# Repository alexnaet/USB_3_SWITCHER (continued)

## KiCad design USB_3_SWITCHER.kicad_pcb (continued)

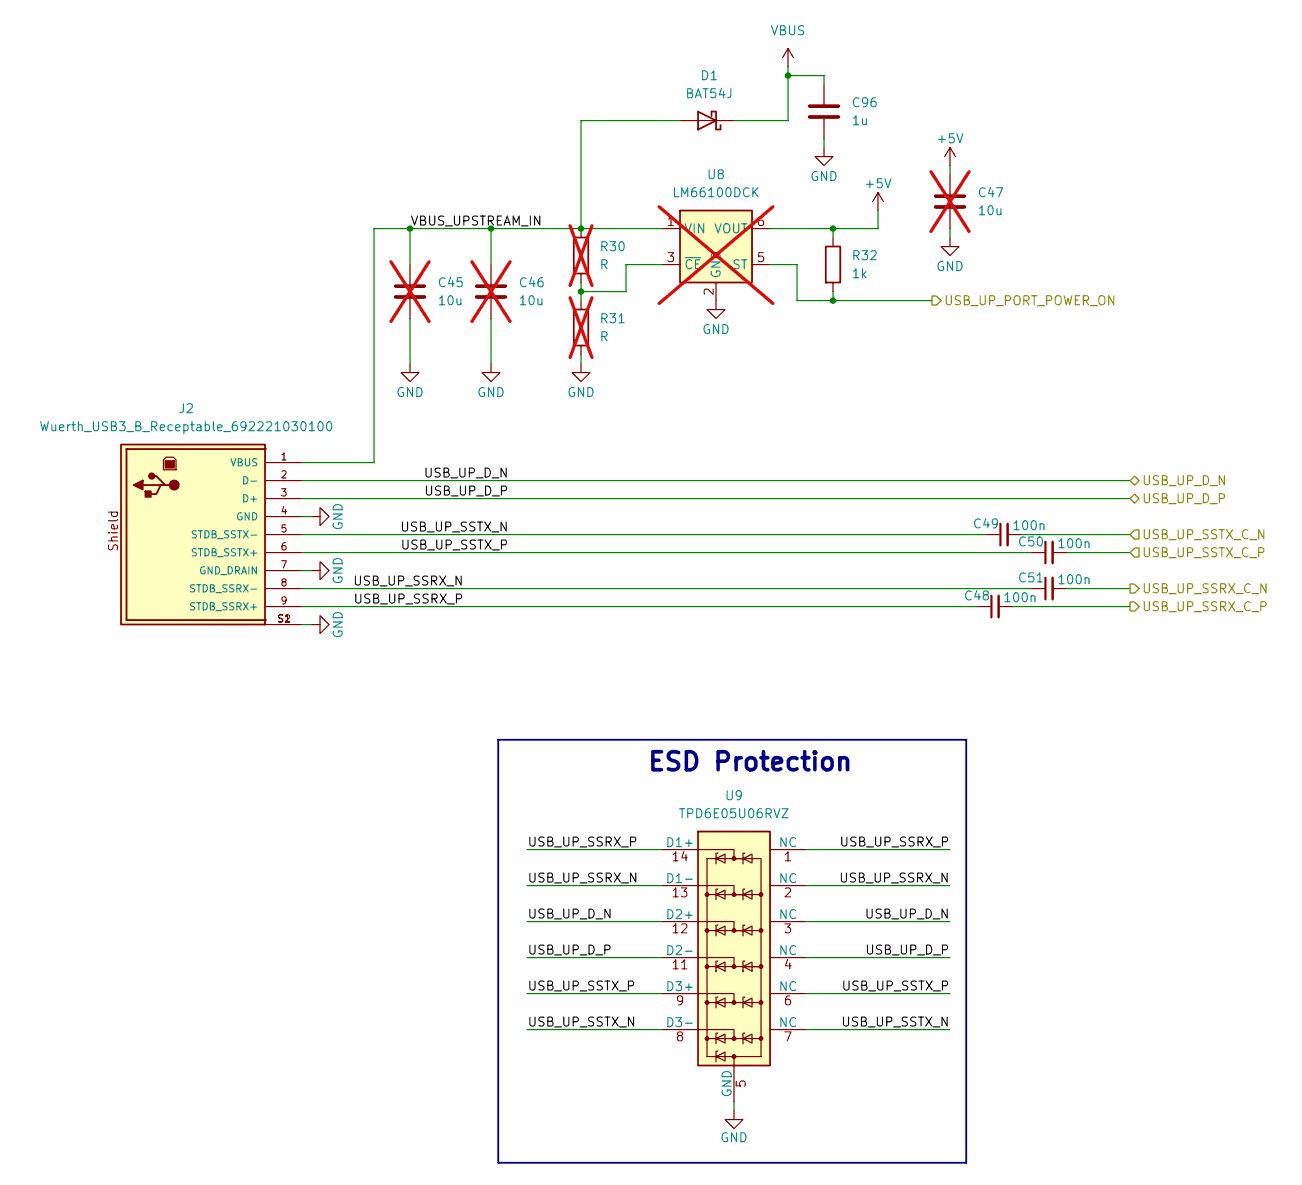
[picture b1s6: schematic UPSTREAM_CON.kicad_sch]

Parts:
C45, C46, C47: 10u; Cap_0603; not fitted
C48, C49, C50, C51: 100n; Cap_0402
C96: 1u; Cap_0603
D1: BAT54J; D_SOD-323F
J2: Wuerth_USB3_B_Receptable_692221030100; Wuerth_USB3B_692221030100; DigiKey_Part_Number 732-3158-ND
R30, R31: R; Res_0402; not fitted
R32: 1k; Res_0402
U8: LM66100DCK; SOT-363_SC-70-6; not fitted
U9: TPD6E05U06RVZ; Texas_R-PUSON-N14

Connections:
+5V: C47.1, R32.1, U8.6 (VOUT); also elsewhere on the board
/HS_MUX/USB_UP1_SSRX_C_N: C51.2; also elsewhere on the board
/HS_MUX/USB_UP1_SSRX_C_P: C48.2; also elsewhere on the board
/HS_MUX/USB_UP1_SSTX_C_N: C49.2; also elsewhere on the board
/HS_MUX/USB_UP1_SSTX_C_P: C50.2; also elsewhere on the board
/POWER_SEQUENCING/USB_UP_PORT1_POWER_ON: R32.2, U8.5 (ST); also elsewhere on the board
/UPSTREAM_CON/USB_UP_D_N: J2.2 (D-), U9.3 (NC), U9.12 (D2+); also elsewhere on the board
/UPSTREAM_CON/USB_UP_D_P: J2.3 (D+), U9.4 (NC), U9.11 (D2-); also elsewhere on the board
/UPSTREAM_CON/USB_UP_SSRX_N: C51.1, J2.8 (STDB_SSRX-), U9.2 (NC), U9.13 (D1-)
/UPSTREAM_CON/USB_UP_SSRX_P: C48.1, J2.9 (STDB_SSRX+), U9.1 (NC), U9.14 (D1+)
/UPSTREAM_CON/USB_UP_SSTX_N: C49.1, J2.5 (STDB_SSTX-), U9.7 (NC), U9.8 (D3-)
/UPSTREAM_CON/USB_UP_SSTX_P: C50.1, J2.6 (STDB_SSTX+), U9.6 (NC), U9.9 (D3+)
/UPSTREAM_CON/VBUS_UPSTREAM_IN: C45.1, C46.1, D1.2 (A), J2.1 (VBUS), R30.1, U8.1 (VIN)
GND: C45.2, C46.2, C47.2, C96.2, J2.4 (GND), J2.7 (GND_DRAIN), J2.S1, J2.S2, R31.2, U8.2 (GND), U9.5 (GND), U9.10 (GND); also elsewhere on the board
unnamed: R30.2, R31.1, U8.3 (~CE)
VBUS: C96.1, D1.1 (K); also elsewhere on the board

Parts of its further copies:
C52, C53, C54: 10u; Cap_0603; not fitted
C55, C56, C57, C58: 100n; Cap_0402
C97: 1u; Cap_0603
D2: BAT54J; D_SOD-323F
J3: Wuerth_USB3_B_Receptable_692221030100; Wuerth_USB3B_692221030100; DigiKey_Part_Number 732-3158-ND
R33, R34: R; Res_0402; not fitted
R35: 1k; Res_0402
U10: LM66100DCK; SOT-363_SC-70-6; not fitted
U11: TPD6E05U06RVZ; Texas_R-PUSON-N14

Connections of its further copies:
+5V: C54.1, R35.1, U10.6 (VOUT); also elsewhere on the board
/HS_MUX/USB_UP2_SSRX_C_N: C58.2; also elsewhere on the board
/HS_MUX/USB_UP2_SSRX_C_P: C55.2; also elsewhere on the board
/HS_MUX/USB_UP2_SSTX_C_N: C56.2; also elsewhere on the board
/HS_MUX/USB_UP2_SSTX_C_P: C57.2; also elsewhere on the board
/POWER_SEQUENCING/USB_UP_PORT2_POWER_ON: R35.2, U10.5 (ST); also elsewhere on the board
/UPSTREAM_CON1/USB_UP_D_N: J3.2 (D-), U11.3 (NC), U11.12 (D2+); also elsewhere on the board
/UPSTREAM_CON1/USB_UP_D_P: J3.3 (D+), U11.4 (NC), U11.11 (D2-); also elsewhere on the board
/UPSTREAM_CON1/USB_UP_SSRX_N: C58.1, J3.8 (STDB_SSRX-), U11.2 (NC), U11.13 (D1-)
/UPSTREAM_CON1/USB_UP_SSRX_P: C55.1, J3.9 (STDB_SSRX+), U11.1 (NC), U11.14 (D1+)
/UPSTREAM_CON1/USB_UP_SSTX_N: C56.1, J3.5 (STDB_SSTX-), U11.7 (NC), U11.8 (D3-)
/UPSTREAM_CON1/USB_UP_SSTX_P: C57.1, J3.6 (STDB_SSTX+), U11.6 (NC), U11.9 (D3+)
/UPSTREAM_CON1/VBUS_UPSTREAM_IN: C52.1, C53.1, D2.2 (A), J3.1 (VBUS), R33.1, U10.1 (VIN)
GND: C52.2, C53.2, C54.2, C97.2, J3.4 (GND), J3.7 (GND_DRAIN), J3.S1, J3.S2, R34.2, U10.2 (GND), U11.5 (GND), U11.10 (GND); also elsewhere on the board
unnamed: R33.2, R34.1, U10.3 (~CE)
VBUS: C97.1, D2.1 (K); also elsewhere on the board

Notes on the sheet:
ESD Protection

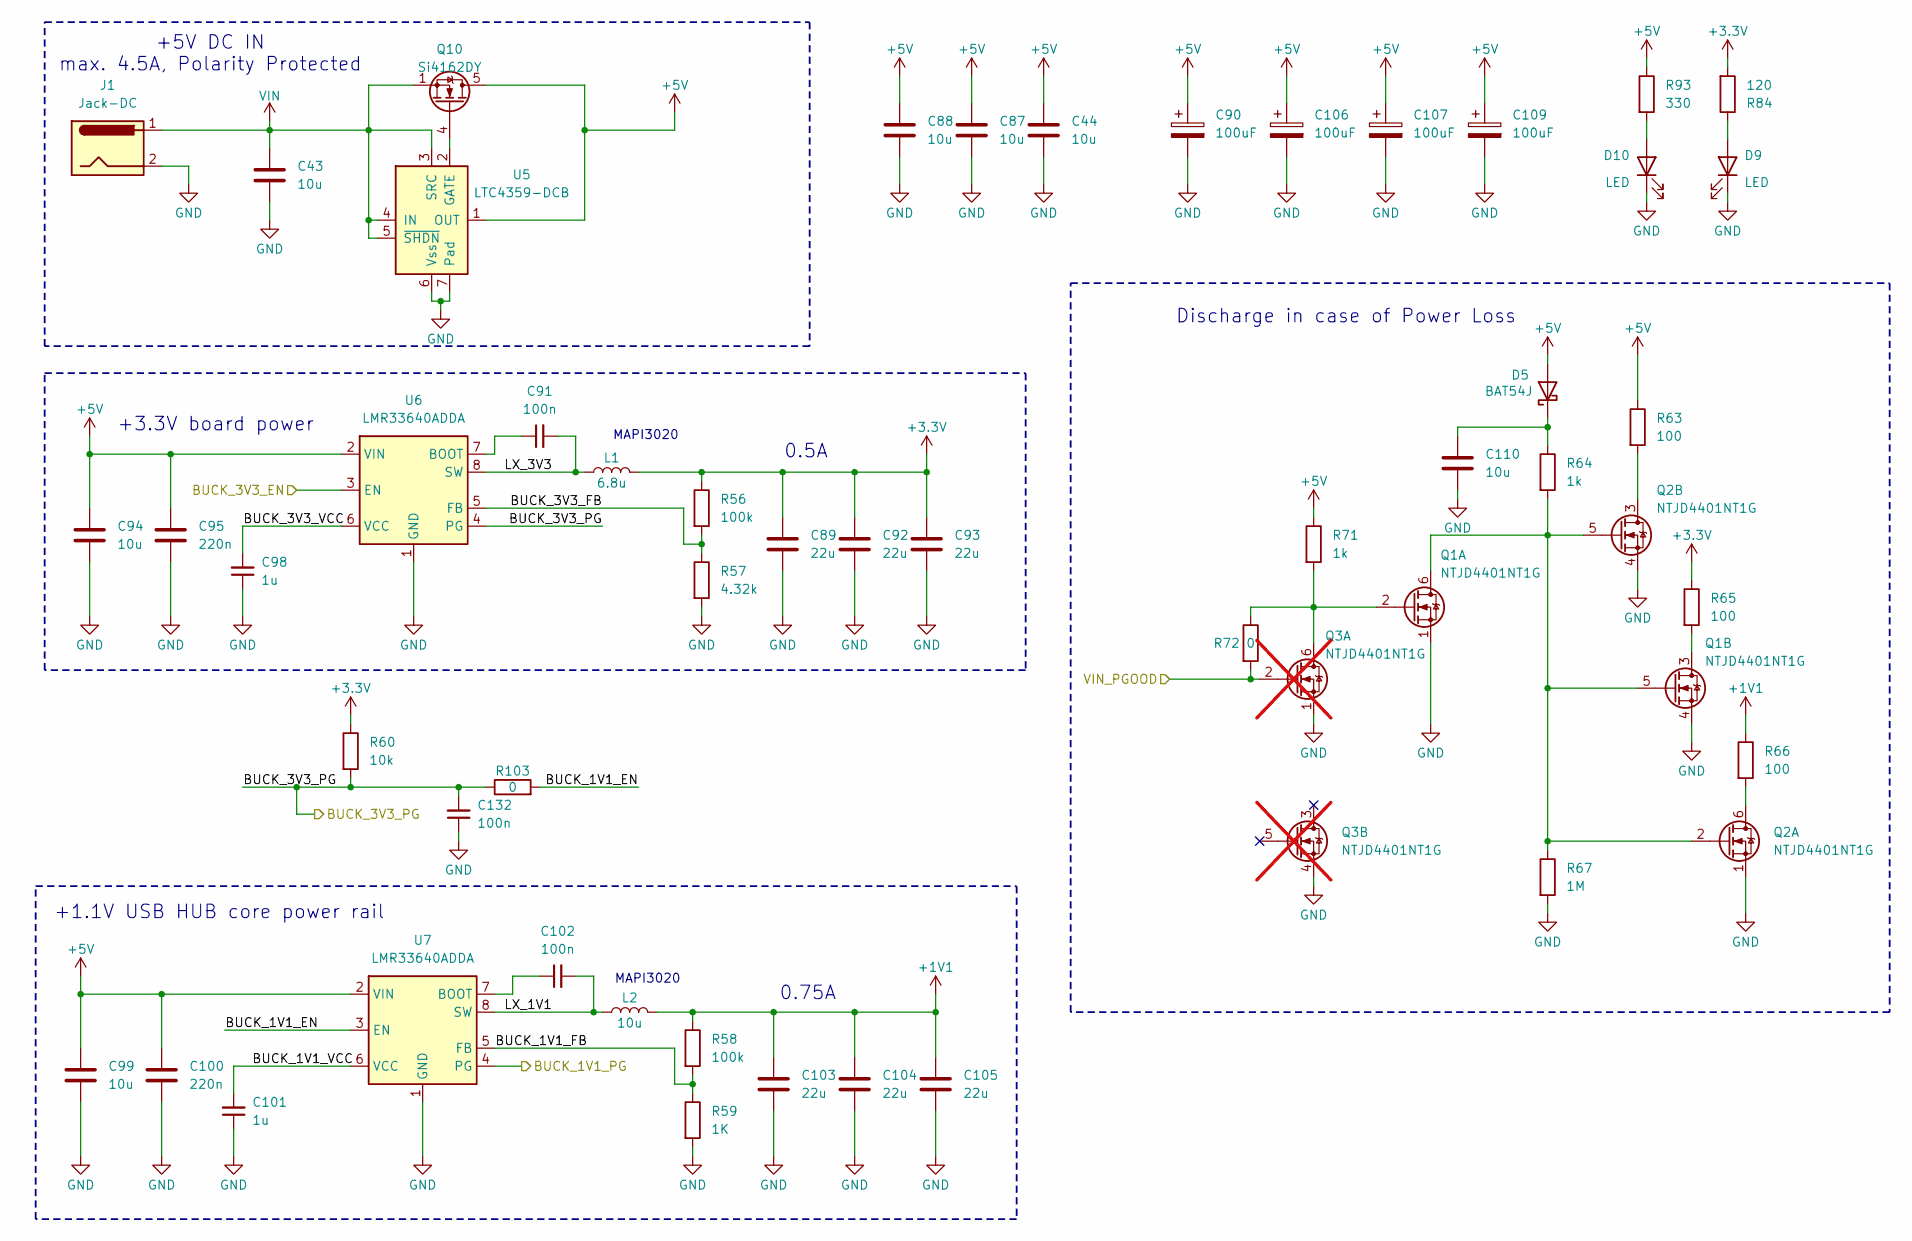
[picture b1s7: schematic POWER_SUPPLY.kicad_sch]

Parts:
C43, C44, C87, C88, C94, C99, C110: 10u; Cap_0603
C89, C92, C93, C103, C104, C105: 22u; Cap_0805
C90, C106, C107, C109: 100uF; CP_Elec_6.3x5.9
C91, C102, C132: 100n; Cap_0402
C95, C100: 220n; Cap_0402
C98, C101: 1u; Cap_0402
D5: BAT54J; D_SOD-323F
D9, D10: LED; LED_0603_1608Metric
J1: Jack-DC; BarrelJack_GCT_DCJ200-10-A_Horizontal
L1: 6.8u; L_Wuerth_MAPI-3020
L2: 10u; L_Wuerth_MAPI-3020
Q1, Q2: NTJD4401NT1G; SOT-363_SC-70-6
Q3: NTJD4401NT1G; SOT-363_SC-70-6; not fitted
Q10: Si4162DY; SOIC-8_3.9x4.9mm_P1.27mm
R56, R58: 100k; Cap_0402
R57: 4.32k; Cap_0402
R59: 1K; Cap_0402
R60: 10k; Res_0402
R63, R65, R66: 100; Res_0402
R64, R71: 1k; Res_0402
R67: 1M; Res_0402
R72: 0; Res_0402
R84: 120; Res_0402
R93: 330; Res_0402
R103: 0; Cap_0402
U5: LTC4359-DCB; DFN-6-1EP_3x2mm_P0.5mm_EP1.65x1.35mm
U6, U7: LMR33640ADDA; Texas_HSOP-8-1EP_3.9x4.9mm_P1.27mm_ThermalVias

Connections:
+1V1: C103.1, C104.1, C105.1, L2.2, R58.1, R66.1; also elsewhere on the board
+3.3V: C89.1, C92.1, C93.1, L1.2, R56.1, R60.1, R65.1, R84.2; also elsewhere on the board
+5V: C44.1, C87.1, C88.1, C90.1, C94.1, C95.1, C99.1, C100.1, C106.1, C107.1, C109.1, D5.2 (A), Q10.5 (D), Q10.6 (D), Q10.7 (D), Q10.8 (D), R63.1, R71.1, R93.1, U5.1 (OUT), U6.2 (VIN), U7.2 (VIN); also elsewhere on the board
/POWER_SEQUENCING/BUCK_1V1_PG: U7.4 (PG); also elsewhere on the board
/POWER_SEQUENCING/BUCK_3V3_EN: U6.3 (EN); also elsewhere on the board
/POWER_SEQUENCING/VIN_PGOOD: Q3.2 (G), R72.2; also elsewhere on the board
/POWER_SUPPLY/BUCK_1V1_EN: R103.2, U7.3 (EN)
/POWER_SUPPLY/BUCK_1V1_FB: R58.2, R59.1, U7.5 (FB)
/POWER_SUPPLY/BUCK_1V1_VCC: C101.2, U7.6 (VCC)
/POWER_SUPPLY/BUCK_3V3_FB: R56.2, R57.1, U6.5 (FB)
/POWER_SUPPLY/BUCK_3V3_PG: C132.2, R60.2, R103.1, U6.4 (PG); also elsewhere on the board
/POWER_SUPPLY/BUCK_3V3_VCC: C98.2, U6.6 (VCC)
/POWER_SUPPLY/LX_1V1: C102.2, L2.1, U7.8 (SW)
/POWER_SUPPLY/LX_3V3: C91.2, L1.1, U6.8 (SW)
GND: C43.2, C44.2, C87.2, C88.2, C89.2, C90.2, C92.2, C93.2, C94.2, C95.2, C98.1, C99.2, C100.2, C101.1, C103.2, C104.2, C105.2, C106.2, C107.2, C109.2, C110.2, C132.1, D9.1 (K), D10.1 (K), J1.2, Q1.1 (S), Q1.4 (S), Q2.1 (S), Q2.4 (S), Q3.1 (S), Q3.4 (S), R57.2, R59.2, R67.2, U5.6 (Vss), U5.7 (Pad), U6.1 (GND), U6.9 (GND), U7.1 (GND), U7.9 (GND); also elsewhere on the board
unnamed: C110.1, D5.1 (K), R64.1
unnamed: D9.2 (A), R84.1
unnamed: D10.2 (A), R93.2
unnamed: Q1.5 (G), Q1.6 (D), Q2.2 (G), Q2.5 (G), R64.2, R67.1
unnamed: Q1.2 (G), Q3.6 (D), R71.2, R72.1
unnamed: Q1.3 (D), R65.2
unnamed: Q2.6 (D), R66.2
unnamed: Q2.3 (D), R63.2
unnamed: Q10.4 (G), U5.2 (GATE)
unnamed: C91.1, U6.7 (BOOT)
unnamed: C102.1, U7.7 (BOOT)
VIN: C43.1, J1.1, Q10.1 (S), Q10.2 (S), Q10.3 (S), U5.3 (SRC), U5.4 (IN), U5.5 (~SHDN)

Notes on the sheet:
+5V DC IN max. 4.5A, Polarity Protected
MAPI3020
+3.3V board power
Discharge in case of Power Loss
0.75A
+1.1V USB HUB core power rail
0.5A

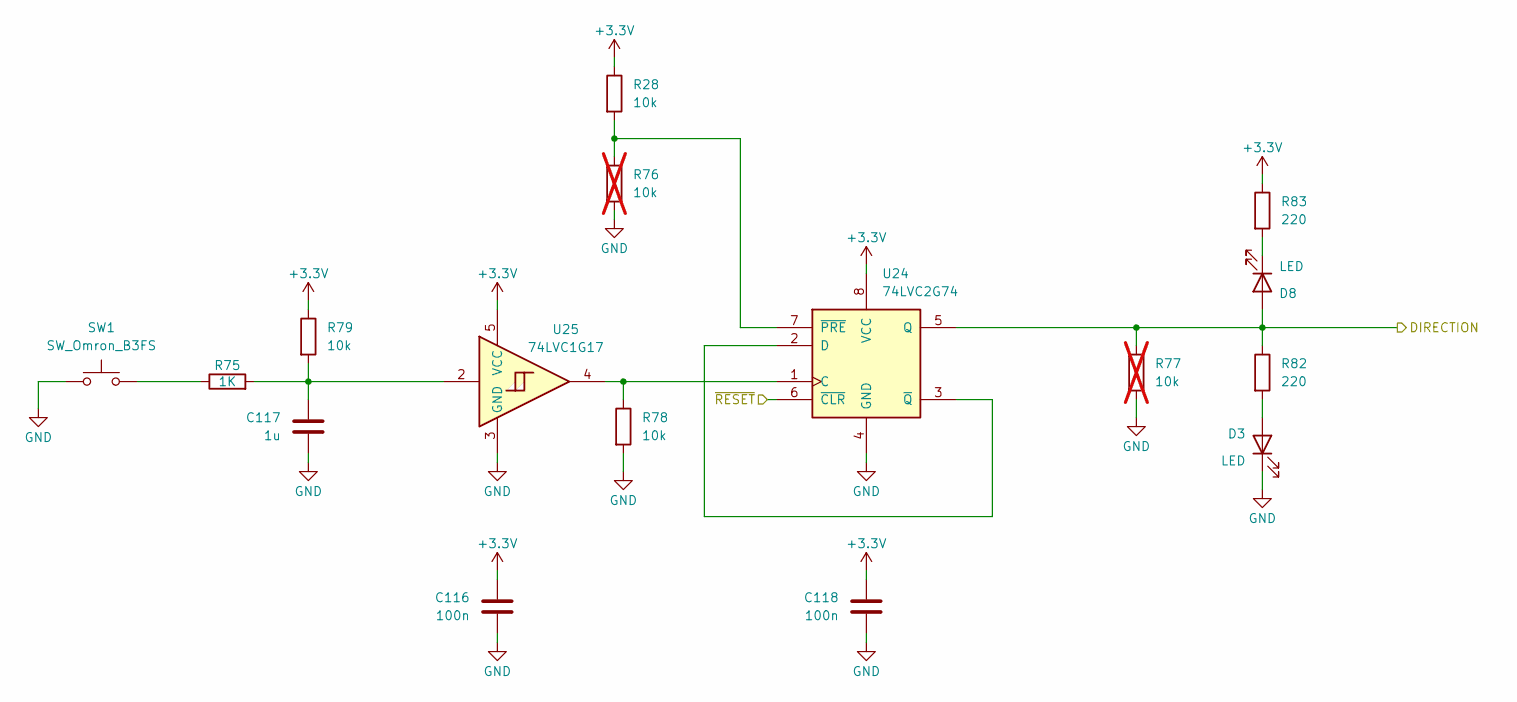
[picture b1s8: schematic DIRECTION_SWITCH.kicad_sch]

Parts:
C116, C118: 100n; Cap_0402
C117: 1u; Cap_0402
D3, D8: LED; LED_0603_1608Metric
R28, R78, R79: 10k; Res_0402
R75: 1K; Cap_0402
R76, R77: 10k; Res_0402; not fitted
R82, R83: 220; Res_0402
SW1: SW_Omron_B3FS; SW_SPST_Omron_B3FS-105xP
U24: 74LVC2G74; SOP50P310X90-8N
U25: 74LVC1G17; SOT-23-5

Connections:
+3.3V: C116.1, C118.1, R28.1, R79.1, R83.1, U24.8 (VCC), U25.5 (VCC); also elsewhere on the board
/DIRECTION_SWITCH/DIRECTION: D8.2 (A), R77.1, R82.1, U24.5 (Q); also elsewhere on the board
/DIRECTION_SWITCH/~RESET: U24.6 (~CLR); also elsewhere on the board
GND: C116.2, C117.2, C118.2, D3.1 (K), R76.2, R77.2, R78.2, SW1.1, U24.4 (GND), U25.3 (GND); also elsewhere on the board
unnamed: C117.1, R75.2, R79.2, U25.2
unnamed: D3.2 (A), R82.2
unnamed: D8.1 (K), R83.2
unnamed: R75.1, SW1.2
unnamed: R78.1, U24.1 (C), U25.4
unnamed: U24.2 (D), U24.3 (~Q)
unnamed: R28.2, R76.1, U24.7 (~PRE)

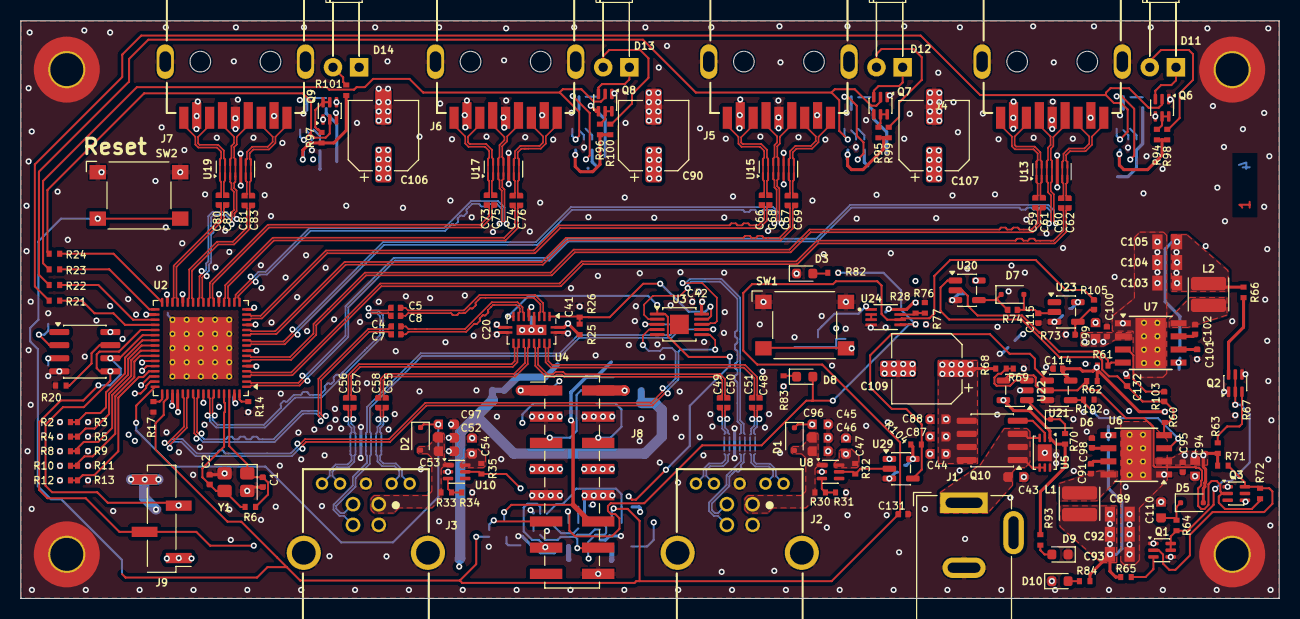
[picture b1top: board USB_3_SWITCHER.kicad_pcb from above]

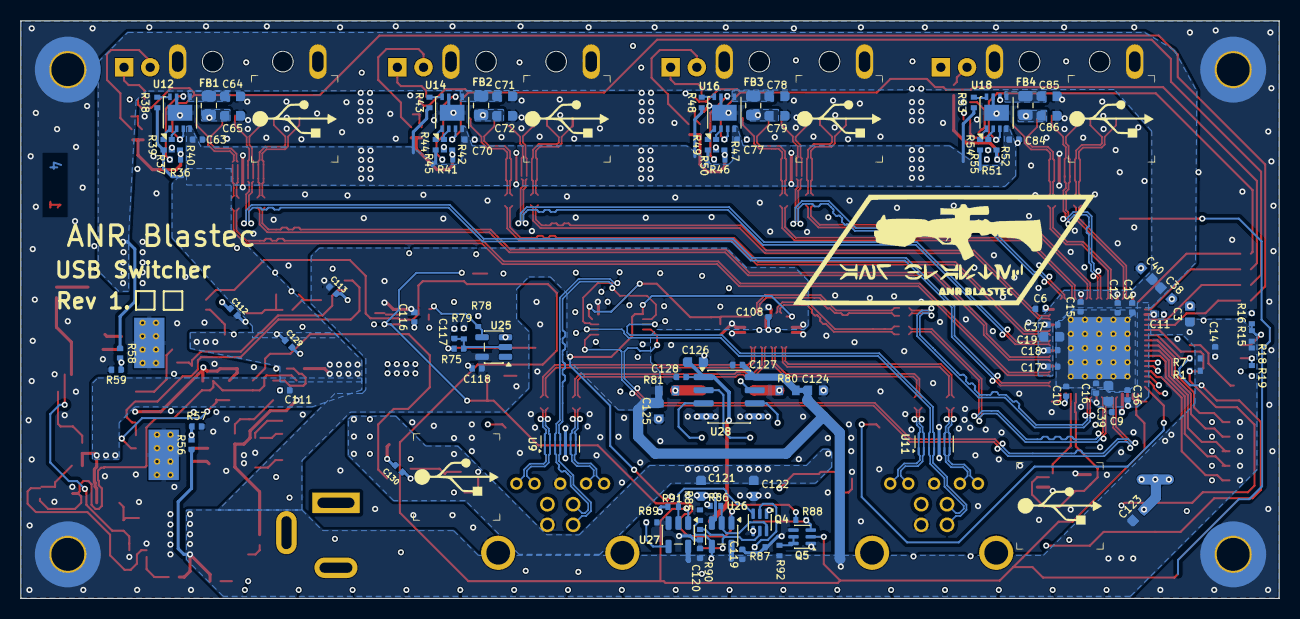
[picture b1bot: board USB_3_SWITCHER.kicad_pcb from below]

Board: 4 copper layers, 122.0 x 56.0 mm, 294 parts (108 on the bottom side), 190 nets.

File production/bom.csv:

Designator,Footprint,Quantity,Value,LCSC Part #
"C1, C2",Cap_0402,2,10p,
"C10, C102, C11, C12, C13, C14, C15, C16, C17, C18, C19, C20, C36, C4, C41, C42, C48, C49, C5, C50, C51, C55, C56, C57, C58, C59, C6, C60, C61, C62, C66, C67, C68, C69, C7, C73, C74, C75, C76, C8, C80, C81, C82, C83, C9, C91",Cap_0402,46,100n,
"C100, C95",Cap_0402,2,220n,
"C101, C63, C70, C77, C84, C98",Cap_0402,6,1u,
"C103, C104, C105, C89, C92, C93",Cap_0805,6,22u,
"C3, C37, C38, C39, C40, C43, C44, C45, C46, C47, C52, C53, C54, C64, C65, C71, C72, C78, C79, C85, C86, C87, C88, C94, C96, C97, C99",Cap_0603,27,10u,
C90,CP_Elec_6.3x5.9,1,100uF,
"D1, D2",D_SOD-323,2,D_Schottky,
"FB1, FB2, FB3, FB4",0805,4,FerriteBead,
J1,BarrelJack_GCT_DCJ200-10-A_Horizontal,1,Jack-DC,
"J2, J3",Wuerth_USB3B_692221030100,2,Wuerth_USB3_B_Receptable_692221030100,
"J4, J5, J6, J7",Wuerth_USB3A_receptible_692122030100,4,Wuerth_USB3_Receptible_692122030100,
J8,PinHeader_2x08_P2.54mm_Vertical_SMD,1,Conn_01x16_MountingPin,
J9,PinHeader_1x04_P2.54mm_Vertical_SMD_Pin1Left,1,Conn_01x04_MountingPin,
L1,L_Coilcraft_XAL7030-272,1,6.8u,
L2,L_Coilcraft_XAL7030-272,1,10u,
"R1, R7",Res_0402,2,3k3,
"R10, R11, R12, R13, R15, R16, R17, R18, R19, R2, R20, R26, R3, R36, R37, R38, R39, R4, R41, R42, R43, R44, R46, R47, R48, R49, R5, R51, R52, R53, R54, R8, R9",Res_0402,33,10k,
R14,Res_0402,1,9.53k,
"R21, R22, R23, R24",Res_0402,4,0,
R25,Res_0402,1,1k,
"R27, R28, R29, R30, R31, R32, R33, R34, R35",Res_0402,9,R,
"R40, R45, R50, R55",Res_0402,4,39k,
"R56, R58",Cap_0402,2,100k,
R57,Cap_0402,1,4.32k,
R59,Cap_0402,1,1K,
R6,Res_0402,1,1M,
U1,SOIC-8_3.9x4.9mm_P1.27mm,1,AT24CS04-SSHM,
"U10, U5, U8",SOT-363_SC-70-6,3,LM66100DCK,
"U11, U13, U15, U17, U19, U9",Texas_R-PUSON-N14,6,TPD6E05U06RVZ,
"U12, U14, U16, U18",DFN-8-1EP_3x3mm_P0.65mm_EP1.55x2.4mm,4,MAX8586,
U2,QFN-64-1EP_9x9mm_P0.5mm_EP6x6mm_ThermalVias,1,TUSB8043A,
U3,VSSOP-10_3x3mm_P0.5mm,1,TS3USB30EDGSR,
U4,WQFN-20-1EP_2.5x4.5mm_P0.5mm_EP1x2.9mm,1,CBTL02043A,
"U6, U7",Texas_HSOP-8-1EP_3.9x4.9mm_P1.27mm_ThermalVias,2,LMR33640ADDA,
Y1,Crystal_SMD_3225-4Pin_3.2x2.5mm,1,24MHz 20ppm,

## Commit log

2026-02-21 Arbeit
2026-02-21 Weiter gearbeitet
    Fast fertig:
    HUB
    Fertig
    Connector (Up and Down)
    MUX
2026-02-21 Footprints Updated
2026-02-22 USB 3 Stecker ausgetauscht
2026-02-23 Weiter gemacht
2026-02-24 Update Layout
2026-02-26 Stuff
2026-02-26 Layout + Schematic weiter gemacht
2026-02-27 Power SupV
2026-02-28 Button & Power Sequencing + Layout
2026-03-01 Diff Pair neu, Layout fast fertig
2026-03-02 Layout nearly finished
2026-03-02 Irgendwas
2026-03-05 Powersequencing
2026-03-11 Schaltplan erweitert, Kleinzeug
2026-03-12 Schematic sheets updated
2026-03-14 Further Update, Layout DRCs resolved
2026-03-17 Power In Circuitry extended for more current
2026-03-17 Restored
2026-03-19 Stuff adapted
